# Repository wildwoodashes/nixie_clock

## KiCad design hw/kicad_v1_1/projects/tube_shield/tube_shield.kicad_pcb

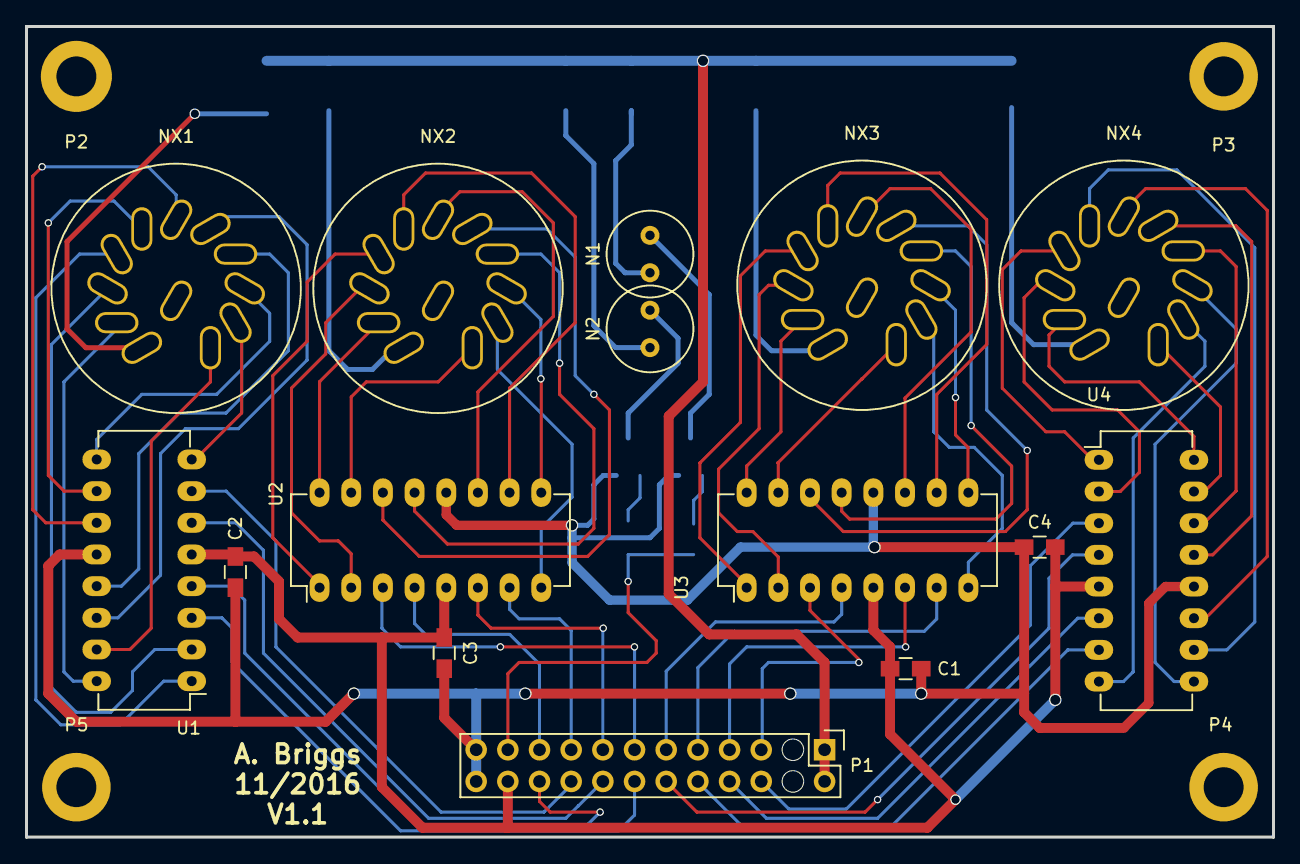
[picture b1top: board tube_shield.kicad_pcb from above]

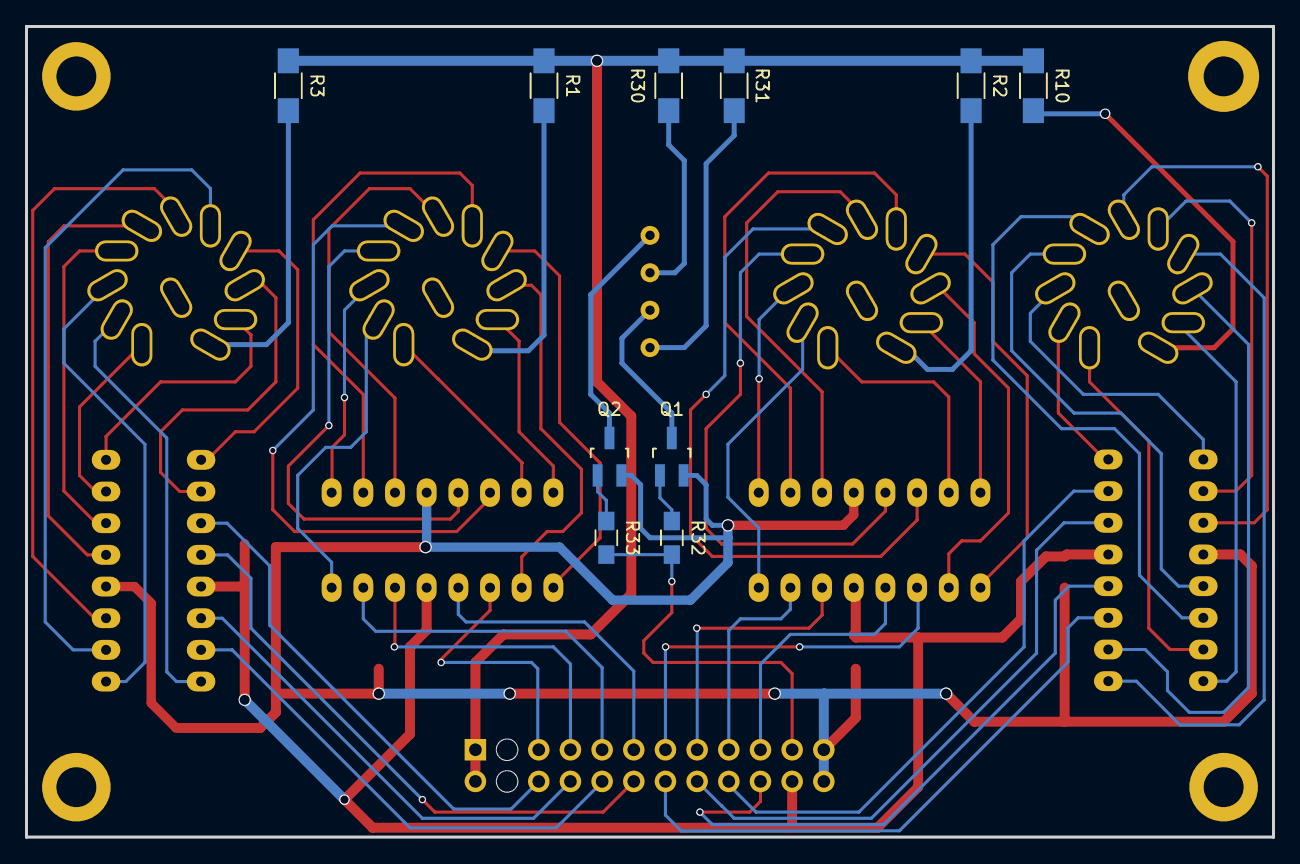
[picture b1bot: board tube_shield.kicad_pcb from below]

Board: 2 copper layers, 100.0 x 65.0 mm, 29 parts (10 on the bottom side), 70 nets.

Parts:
C1, C2, C3, C4: 0.1u; C_0805_HandSoldering
N1, N2: C2A; neon_ind
NX1, NX2, NX3, NX4: IN-8; pl27-1pd
P1: CONN_02X12_isolate_hv; Pin_Header_Straight_2x12_isolate_hv
P2: CONN_01X01; MountingHole_3.2mm_M3_ISO7380_Pad
P3, P4, P5: CONN_01X01; MountingHole_3.2mm_M3_ISO14580_Pad
Q1, Q2: MMBTA42; SOT-23_Handsoldering
R1, R2, R10: 15k; R_1206_HandSoldering
R3: 12k; R_1206_HandSoldering
R30, R31: 100k; R_1206_HandSoldering
R32, R33: 4.7k; R_0805_HandSoldering
U1, U2, U3, U4: K155ID1; DIP-16_W7.62mm_LongPads

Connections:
+5V: C1.1, C2.1, C3.1, C4.1, P1.22, U1.5, U2.5, U3.5, U4.5
+180V: P1.1, P1.2, R1.1, R2.1, R3.1, R10.1, R30.2, R31.2
/COL_SEL: P1.21, R32.2, R33.2
/N0_SEL_A: P1.14, U1.3
/N0_SEL_B: P1.16, U1.6
/N0_SEL_C: P1.18, U1.7
/N0_SEL_D: P1.20, U1.4
/N1_SEL_A: P1.13, U2.3
/N1_SEL_B: P1.15, U2.6
/N1_SEL_C: P1.17, U2.7
/N1_SEL_D: P1.19, U2.4
/N2_SEL_A: P1.5, U3.3
/N2_SEL_B: P1.7, U3.6
/N2_SEL_C: P1.9, U3.7
/N2_SEL_D: P1.11, U3.4
/N3_SEL_A: P1.6, U4.3
/N3_SEL_B: P1.8, U4.6
/N3_SEL_C: P1.10, U4.7
/N3_SEL_D: P1.12, U4.4
/Nixie Tubes/N0_A: NX1.11, R10.2
/Nixie Tubes/N0_CAT0: NX1.10, U1.16
/Nixie Tubes/N0_CAT1: NX1.1, U1.15
/Nixie Tubes/N0_CAT2: NX1.2, U1.8
/Nixie Tubes/N0_CAT3: NX1.3, U1.9
/Nixie Tubes/N0_CAT4: NX1.4, U1.13
/Nixie Tubes/N0_CAT5: NX1.5, U1.14
/Nixie Tubes/N0_CAT6: NX1.6, U1.11
/Nixie Tubes/N0_CAT7: NX1.7, U1.10
/Nixie Tubes/N0_CAT8: NX1.8, U1.1
/Nixie Tubes/N0_CAT9: NX1.9, U1.2
/Nixie Tubes/N1_A: NX2.11, R2.2
/Nixie Tubes/N1_CAT0: NX2.10, U2.16
/Nixie Tubes/N1_CAT1: NX2.1, U2.15
/Nixie Tubes/N1_CAT2: NX2.2, U2.8
/Nixie Tubes/N1_CAT3: NX2.3, U2.9
/Nixie Tubes/N1_CAT4: NX2.4, U2.13
/Nixie Tubes/N1_CAT5: NX2.5, U2.14
/Nixie Tubes/N1_CAT6: NX2.6, U2.11
/Nixie Tubes/N1_CAT7: NX2.7, U2.10
/Nixie Tubes/N1_CAT8: NX2.8, U2.1
/Nixie Tubes/N1_CAT9: NX2.9, U2.2
/Nixie Tubes/N2_A: NX3.11, R1.2
/Nixie Tubes/N2_CAT0: NX3.10, U3.16
/Nixie Tubes/N2_CAT1: NX3.1, U3.15
/Nixie Tubes/N2_CAT2: NX3.2, U3.8
/Nixie Tubes/N2_CAT3: NX3.3, U3.9
/Nixie Tubes/N2_CAT4: NX3.4, U3.13
/Nixie Tubes/N2_CAT5: NX3.5, U3.14
/Nixie Tubes/N2_CAT6: NX3.6, U3.11
/Nixie Tubes/N2_CAT7: NX3.7, U3.10
/Nixie Tubes/N2_CAT8: NX3.8, U3.1
/Nixie Tubes/N2_CAT9: NX3.9, U3.2
/Nixie Tubes/N3_A: NX4.11, R3.2
/Nixie Tubes/N3_CAT0: NX4.10, U4.16
/Nixie Tubes/N3_CAT1: NX4.1, U4.15
/Nixie Tubes/N3_CAT2: NX4.2, U4.8
/Nixie Tubes/N3_CAT3: NX4.3, U4.9
/Nixie Tubes/N3_CAT4: NX4.5, U4.13
/Nixie Tubes/N3_CAT5: NX4.4, U4.14
/Nixie Tubes/N3_CAT6: NX4.6, U4.11
/Nixie Tubes/N3_CAT7: NX4.7, U4.10
/Nixie Tubes/N3_CAT8: NX4.8, U4.1
/Nixie Tubes/N3_CAT9: NX4.9, U4.2
GND: C1.2, C2.2, C3.2, C4.2, P1.23, P1.24, Q1.2, Q2.2, U1.12, U2.12, U3.12, U4.12
unnamed: N1.1, R30.1
unnamed: N1.2, Q2.3
unnamed: N2.1, R31.1
unnamed: N2.2, Q1.3
unnamed: Q1.1, R32.1
unnamed: Q2.1, R33.1

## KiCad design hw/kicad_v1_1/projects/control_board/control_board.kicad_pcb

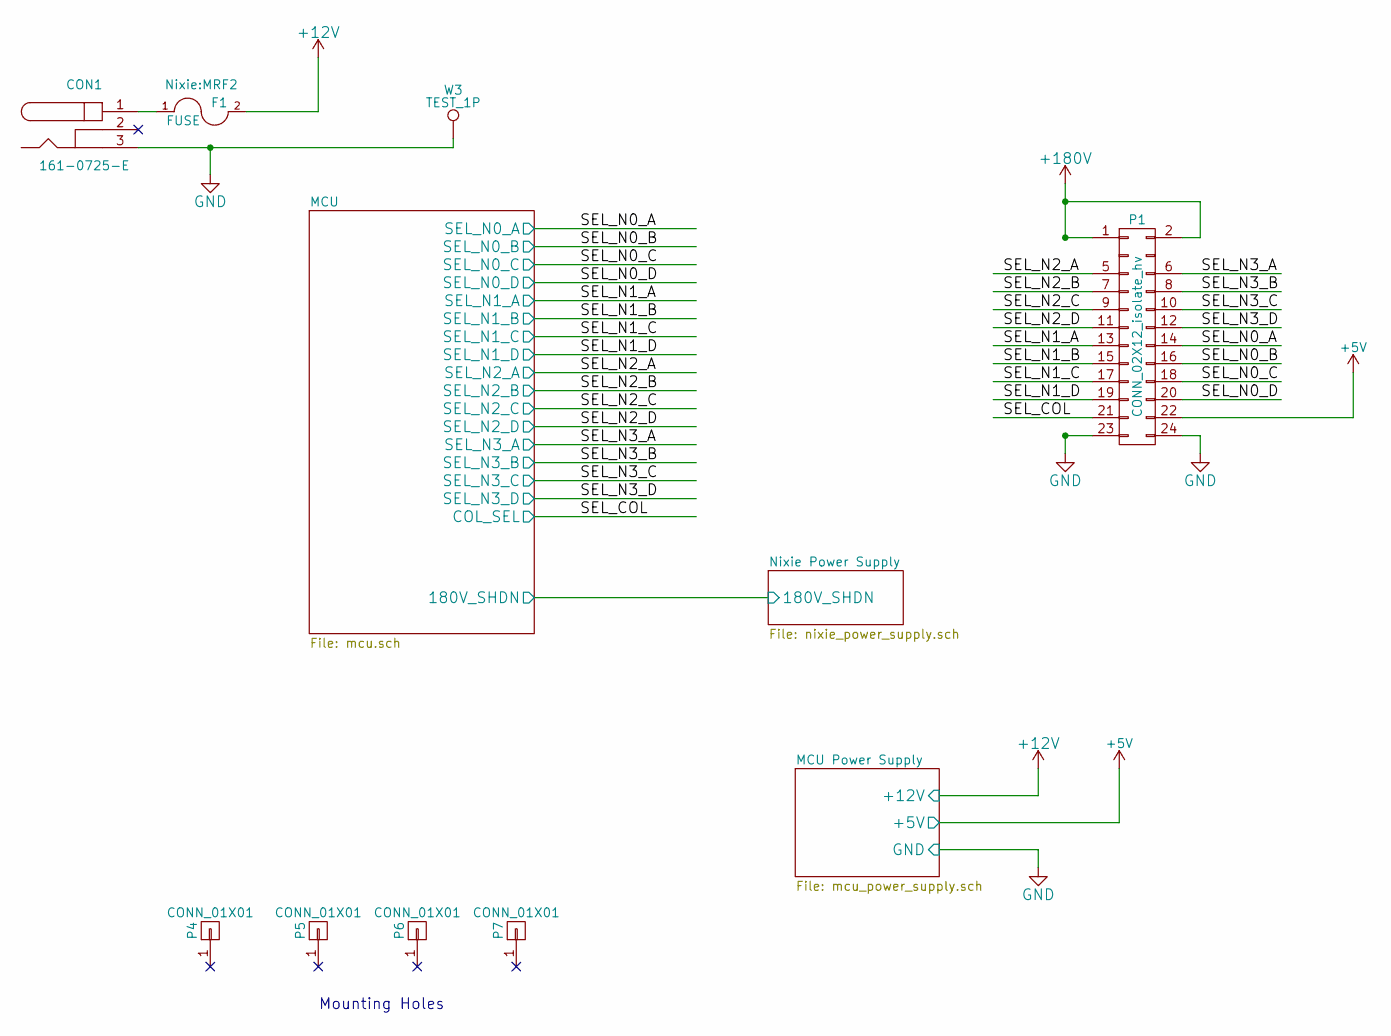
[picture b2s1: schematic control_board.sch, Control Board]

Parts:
CON1: 161-0725-E
F1: FUSE; MRF2
P1: CONN_02X12_isolate_hv
P4, P5, P6, P7: CONN_01X01; MountingHole_3.2mm_M3_ISO7380_Pad
W3: TEST_1P; Test_Point_Keystone_5019_Minature

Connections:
+5V: P1.22; also elsewhere on the board
+12V: F1.2; also elsewhere on the board
+180V: P1.1, P1.2; also elsewhere on the board
/SEL_COL: P1.21; also elsewhere on the board
/SEL_N0_A: P1.14; also elsewhere on the board
/SEL_N0_B: P1.16; also elsewhere on the board
/SEL_N0_C: P1.18; also elsewhere on the board
/SEL_N0_D: P1.20; also elsewhere on the board
/SEL_N1_A: P1.13; also elsewhere on the board
/SEL_N1_B: P1.15; also elsewhere on the board
/SEL_N1_C: P1.17; also elsewhere on the board
/SEL_N1_D: P1.19; also elsewhere on the board
/SEL_N2_A: P1.5; also elsewhere on the board
/SEL_N2_B: P1.7; also elsewhere on the board
/SEL_N2_C: P1.9; also elsewhere on the board
/SEL_N2_D: P1.11; also elsewhere on the board
/SEL_N3_A: P1.6; also elsewhere on the board
/SEL_N3_B: P1.8; also elsewhere on the board
/SEL_N3_C: P1.10; also elsewhere on the board
/SEL_N3_D: P1.12; also elsewhere on the board
GND: CON1.3, P1.23, P1.24, W3.1; also elsewhere on the board
unnamed: CON1.1, F1.1

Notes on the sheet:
Mounting Holes

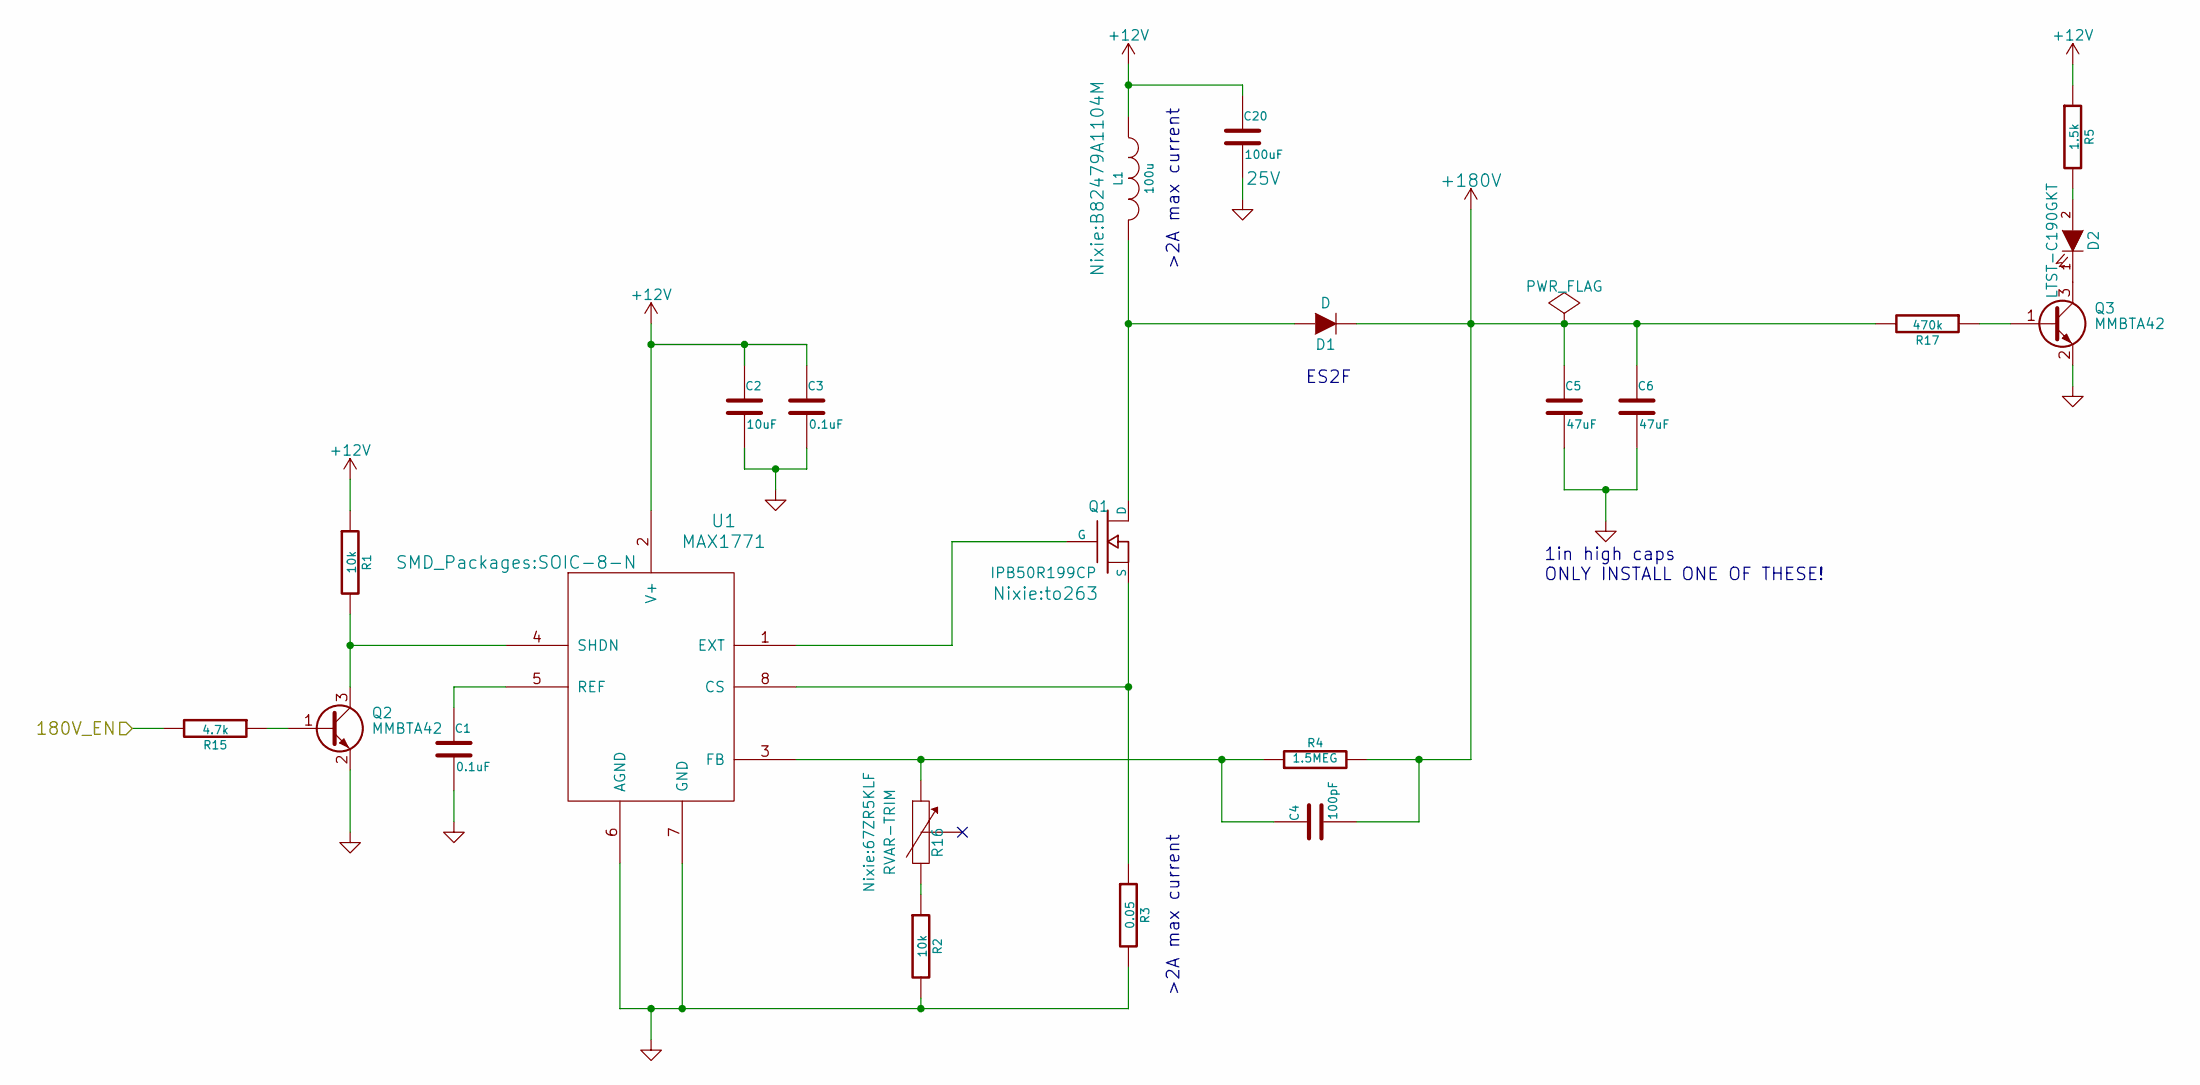
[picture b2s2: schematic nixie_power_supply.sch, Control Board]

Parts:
C1, C3: 0.1uF; C_0805_HandSoldering
C2: 10uF; C_1210_HandSoldering
C4: 100pF; C_0805_HandSoldering
C5, C6: 47uF; C_Radial_D12.5_L25_P5
C20: 100uF; c_elec_6.3x7.7; Voltage 25V
D1: D; DO-214AA-2
D2: LTST-C190GKT; LED_0603
L1: 100u; B82479A1104M
Q1: IPB50R199CP; to263
Q2, Q3: MMBTA42; SOT-23_Handsoldering
R1, R2: 10k; R_0805_HandSoldering
R3: 0.05; R_0805_HandSoldering
R4: 1.5MEG; R_1206_HandSoldering
R5: 1.5k; R_0805_HandSoldering
R15: 4.7k; R_0805_HandSoldering
R16: RVAR-TRIM; 67ZR5KLF
R17: 470k; R_0805_HandSoldering
U1: MAX1771; SOIC-8-N

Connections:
+12V: C2.1, C3.1, C20.1, L1.1, R1.1, R5.1, U1.2 (V+); also elsewhere on the board
+180V: C4.2, C5.1, C6.1, D1.1 (K), R4.2, R17.2; also elsewhere on the board
GND: C1.2, C2.2, C3.2, C5.2, C6.2, C20.2, Q2.2 (E), Q3.2 (E), R2.2, R3.2, U1.6 (AGND), U1.7 (GND); also elsewhere on the board
unnamed: C1.1, U1.5 (REF)
unnamed: C4.1, R4.1, R16.1, U1.3 (FB)
unnamed: D1.2 (A), L1.2, Q1.2 (D)
unnamed: D2.1 (K), Q3.3 (C)
unnamed: D2.2 (A), R5.2
unnamed: Q1.1 (G), U1.1 (EXT)
unnamed: Q1.3 (S), R3.1, U1.8 (CS)
unnamed: Q2.1 (B), R15.1
unnamed: Q3.1 (B), R17.1
unnamed: R2.1, R16.2

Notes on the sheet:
1in high caps ONLY INSTALL ONE OF THESE!
ES2F
>2A max current

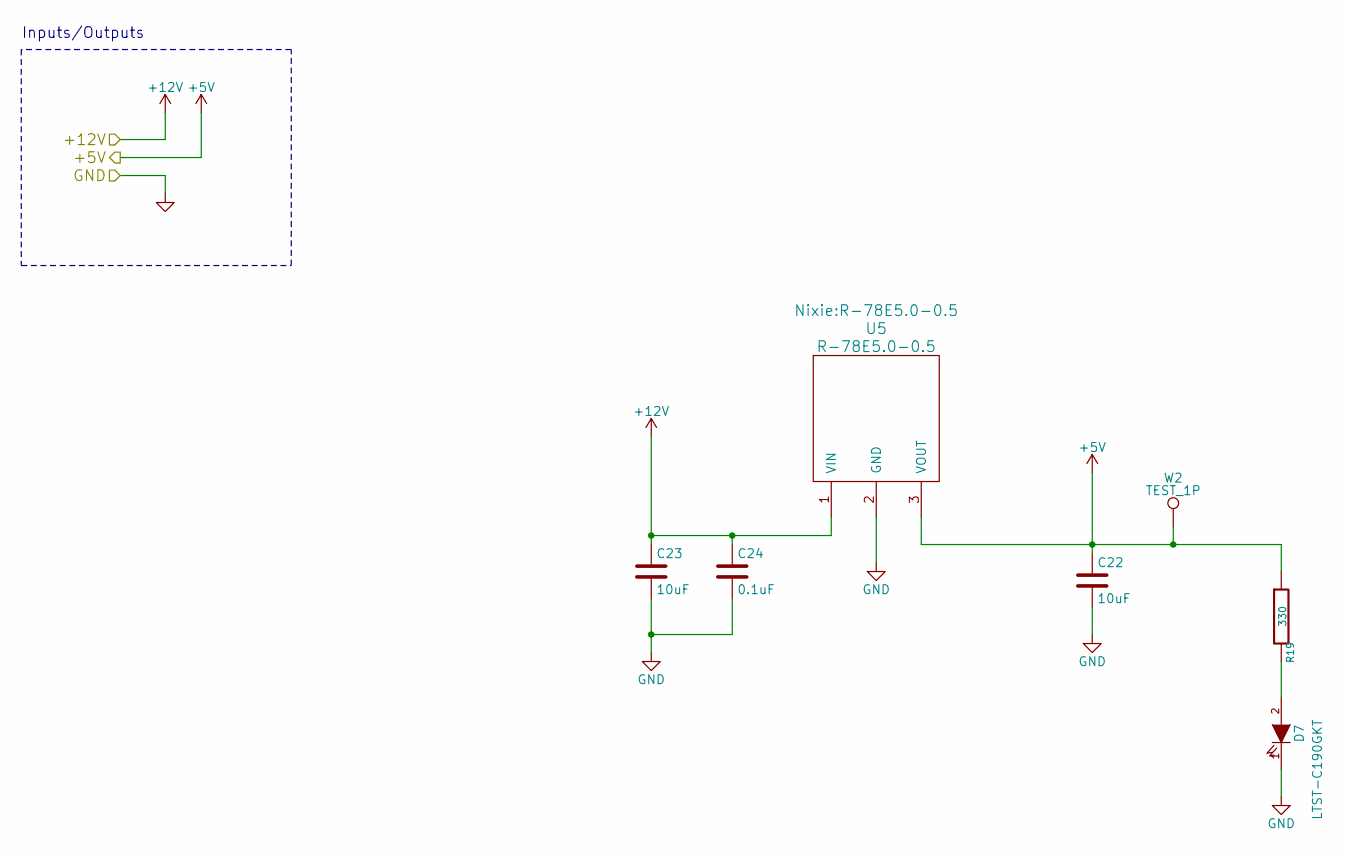
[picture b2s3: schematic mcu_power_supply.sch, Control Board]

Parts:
C22, C23: 10uF; C_0805_HandSoldering
C24: 0.1uF; C_0805_HandSoldering
D7: LTST-C190GKT; LED_0603
R19: 330; R_0805_HandSoldering
U5: R-78E5.0-0.5
W2: TEST_1P; Measurement_Point_Round-TH_Big

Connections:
+5V: C22.1, R19.1, U5.3 (VOUT), W2.1; also elsewhere on the board
+12V: C23.1, C24.1, U5.1 (VIN); also elsewhere on the board
GND: C22.2, C23.2, C24.2, D7.1 (K), U5.2 (GND); also elsewhere on the board
unnamed: D7.2 (A), R19.2

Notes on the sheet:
Inputs/Outputs

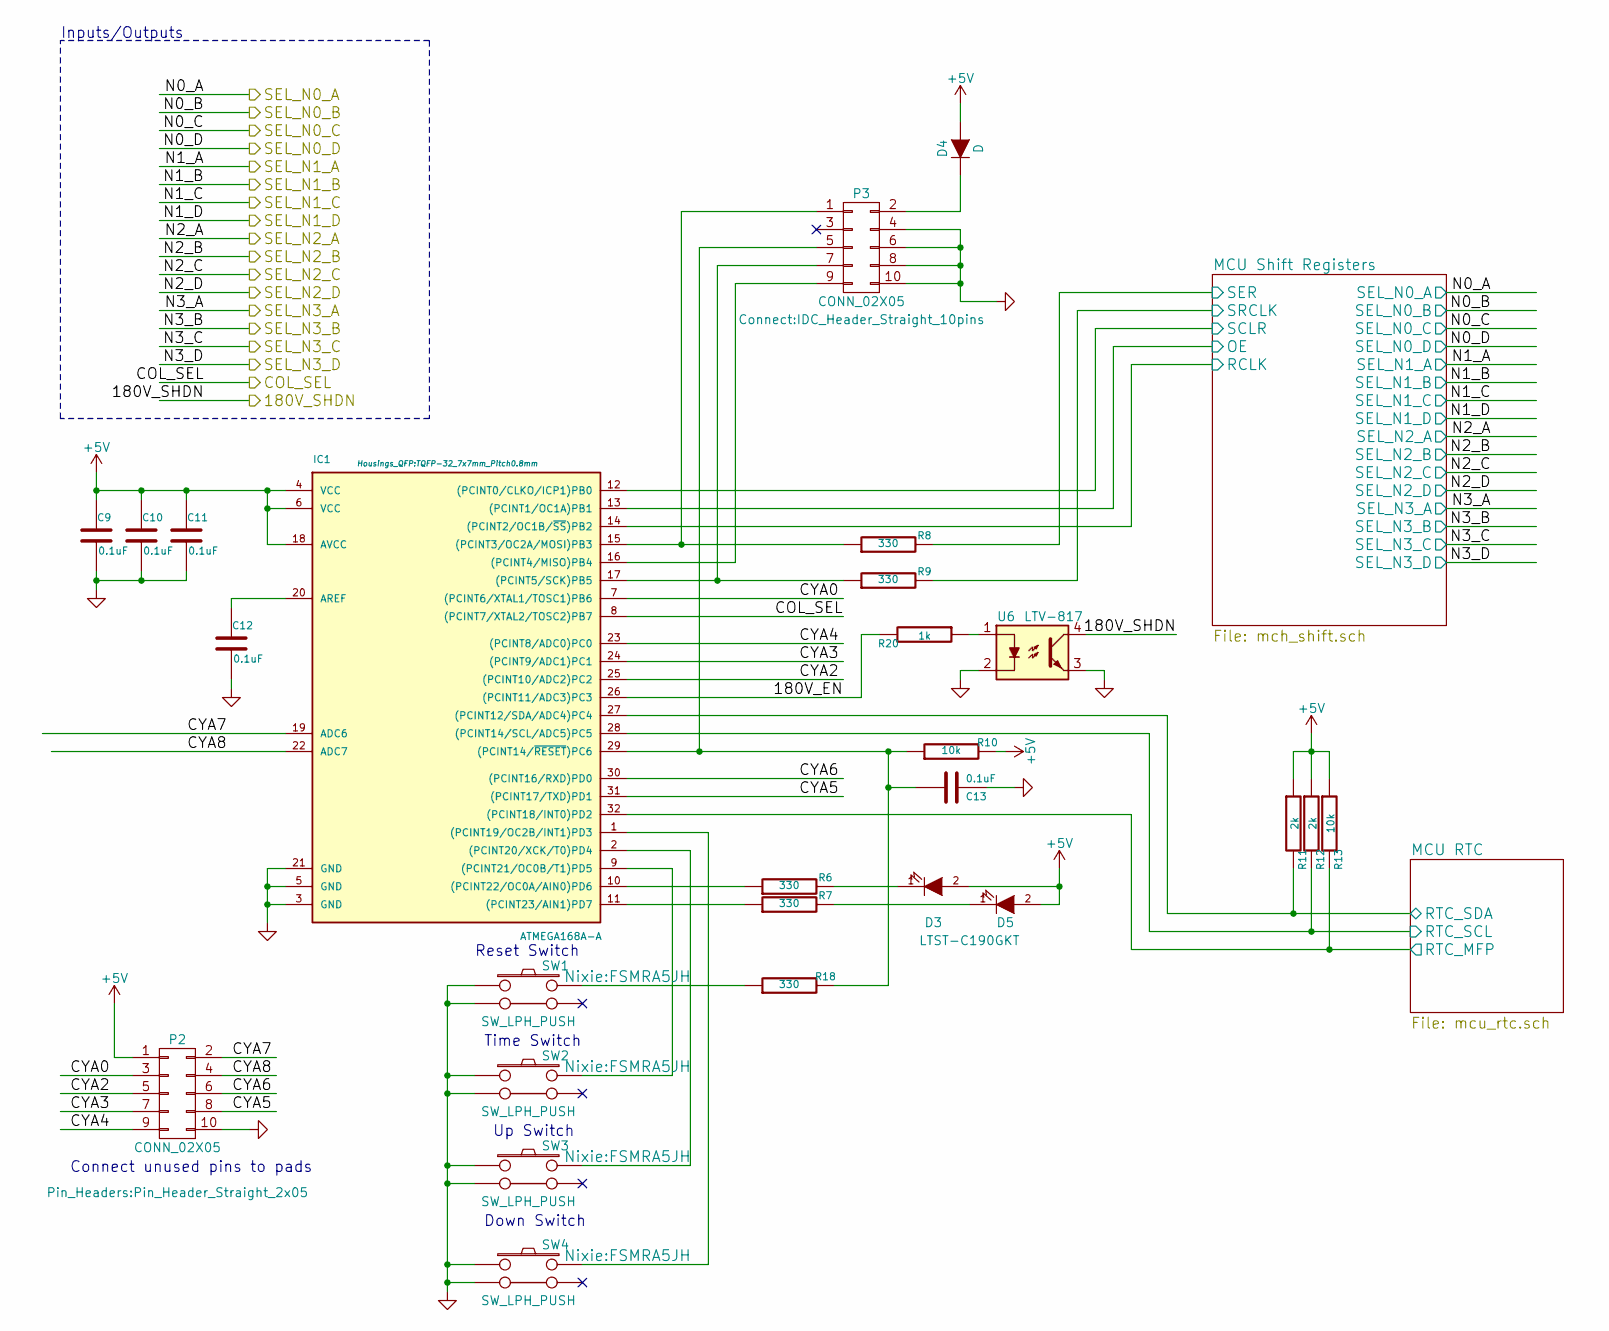
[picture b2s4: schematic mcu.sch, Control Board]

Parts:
C9, C10, C11, C12, C13: 0.1uF; C_0805_HandSoldering
D3, D5: LTST-C190GKT; LED_0603
D4: D; SOD-523-2
IC1: ATMEGA168A-A; TQFP-32_7x7mm_Pitch0.8mm
P2: CONN_02X05; Pin_Header_Straight_2x05
P3: CONN_02X05; IDC_Header_Straight_10pins
R6, R7, R8, R9, R18: 330; R_0805_HandSoldering
R10, R13: 10k; R_0805_HandSoldering
R11, R12: 2k; R_0805_HandSoldering
R20: 1k; R_0805_HandSoldering
SW1, SW2, SW3, SW4: SW_LPH_PUSH; FSMRA5JH
U6: LTV-817; Optocoupler_SMD_LTV-817S

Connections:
+5V: C9.1, C10.1, C11.1, D3.2 (A), D4.2 (A), D5.2 (A), IC1.4 (VCC), IC1.6 (VCC), IC1.18 (AVCC), P2.1, R10.2, R11.1, R12.1, R13.1; also elsewhere on the board
/MCU/180V_EN: IC1.26 ((PCINT11/ADC3)PC3), R20.2
/MCU/CYA0: IC1.7 ((PCINT6/XTAL1/TOSC1)PB6), P2.3
/MCU/CYA2: IC1.25 ((PCINT10/ADC2)PC2), P2.5
/MCU/CYA3: IC1.24 ((PCINT9/ADC1)PC1), P2.7
/MCU/CYA4: IC1.23 ((PCINT8/ADC0)PC0), P2.9
/MCU/CYA5: IC1.31 ((PCINT17/TXD)PD1), P2.8
/MCU/CYA6: IC1.30 ((PCINT16/RXD)PD0), P2.6
/MCU/CYA7: IC1.19 (ADC6), P2.2
/MCU/CYA8: IC1.22 (ADC7), P2.4
/MCU/MCU RTC/RTC_MFP: IC1.32 ((PCINT18/INT0)PD2), R13.2; also elsewhere on the board
/MCU/MCU RTC/RTC_SCL: IC1.28 ((PCINT14/SCL/ADC5)PC5), R12.2; also elsewhere on the board
/MCU/MCU RTC/RTC_SDA: IC1.27 ((PCINT12/SDA/ADC4)PC4), R11.2; also elsewhere on the board
/MCU/MCU Shift Registers/OE: IC1.13 ((PCINT1/OC1A)PB1); also elsewhere on the board
/MCU/MCU Shift Registers/RCLK: IC1.14 ((PCINT2/OC1B/~SS~)PB2); also elsewhere on the board
/MCU/MCU Shift Registers/SCLR: IC1.12 ((PCINT0/CLKO/ICP1)PB0); also elsewhere on the board
/MCU/MCU Shift Registers/SER: R8.2; also elsewhere on the board
/MCU/MCU Shift Registers/SRCLK: R9.2; also elsewhere on the board
/SEL_COL: IC1.8 ((PCINT7/XTAL2/TOSC2)PB7); also elsewhere on the board
GND: C9.2, C10.2, C11.2, C12.2, C13.2, IC1.3 (GND), IC1.5 (GND), IC1.21 (GND), P2.10, P3.4, P3.6, P3.8, P3.10, SW1.1, SW1.4, SW2.1, SW2.4, SW3.1, SW3.4, SW4.1, SW4.4, U6.2, U6.3; also elsewhere on the board
unnamed: C12.1, IC1.20 (AREF)
unnamed: C13.1, IC1.29 ((PCINT14/~RESET~)PC6), P3.5, R10.1, R18.2
unnamed: D3.1 (K), R6.2
unnamed: D4.1 (K), P3.2
unnamed: D5.1 (K), R7.2
unnamed: IC1.1 ((PCINT19/OC2B/INT1)PD3), SW4.2
unnamed: IC1.2 ((PCINT20/XCK/T0)PD4), SW3.2
unnamed: IC1.9 ((PCINT21/OC0B/T1)PD5), SW2.2
unnamed: IC1.10 ((PCINT22/OC0A/AIN0)PD6), R6.1
unnamed: IC1.11 ((PCINT23/AIN1)PD7), R7.1
unnamed: IC1.15 ((PCINT3/OC2A/MOSI)PB3), P3.1, R8.1
unnamed: IC1.16 ((PCINT4/MISO)PB4), P3.9
unnamed: IC1.17 ((PCINT5/SCK)PB5), P3.7, R9.1
unnamed: R18.1, SW1.2
unnamed: R20.1, U6.1

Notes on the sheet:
Inputs/Outputs
Reset Switch
Time Switch
Up Switch
Down Switch
Connect unused pins to pads

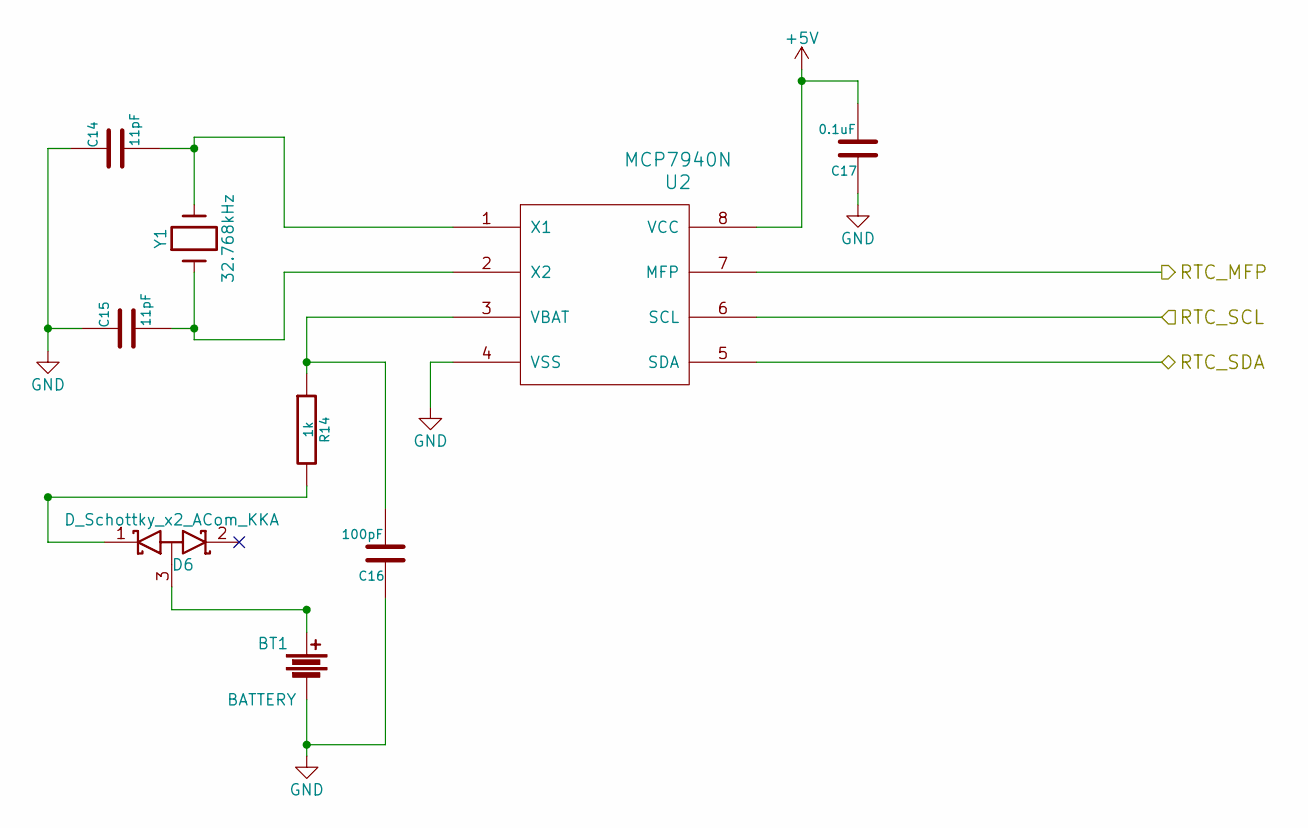
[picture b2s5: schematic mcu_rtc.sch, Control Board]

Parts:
BT1: BATTERY; smtu2032-c
C14, C15: 11pF; C_0603_HandSoldering
C16: 100pF; C_0805_HandSoldering
C17: 0.1uF; C_0805_HandSoldering
D6: D_Schottky_x2_ACom_KKA; SOT-323
R14: 1k; R_0805_HandSoldering
U2: MCP7940N; SOIC-8_3.9x4.9mm_Pitch1.27mm
Y1: 32.768kHz; ABS25

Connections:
+5V: C17.2, U2.8 (VCC); also elsewhere on the board
/MCU/MCU RTC/RTC_MFP: U2.7 (MFP); also elsewhere on the board
/MCU/MCU RTC/RTC_SCL: U2.6 (SCL); also elsewhere on the board
/MCU/MCU RTC/RTC_SDA: U2.5 (SDA); also elsewhere on the board
GND: BT1.2, C14.1, C15.1, C16.1, C17.1, U2.4 (VSS); also elsewhere on the board
unnamed: BT1.1, D6.3 (A)
unnamed: C14.2, U2.1 (X1), Y1.2
unnamed: C15.2, U2.2 (X2), Y1.1
unnamed: C16.2, R14.1, U2.3 (VBAT)
unnamed: D6.1 (K), R14.2

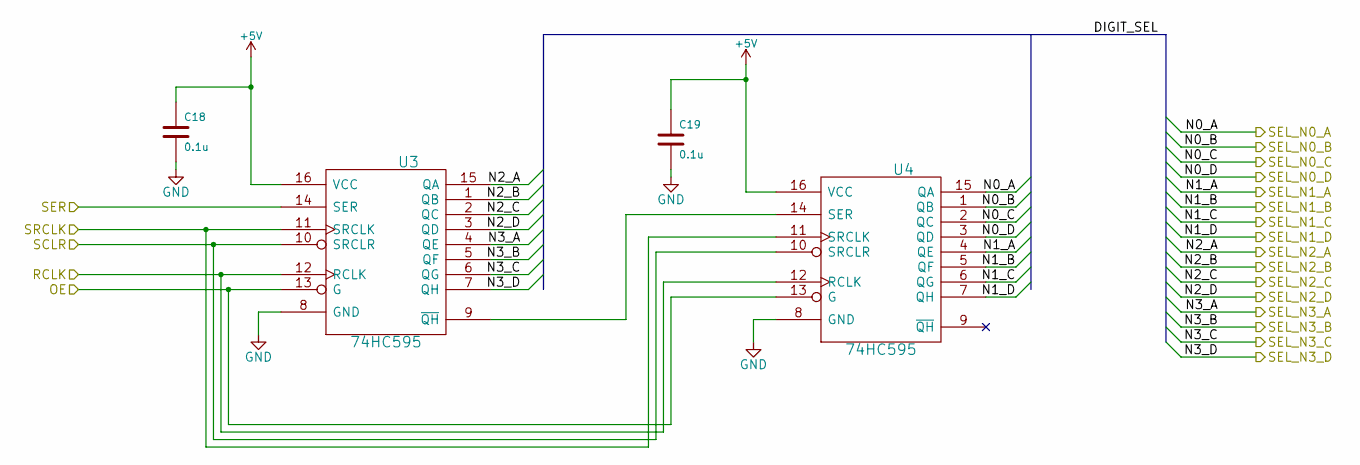
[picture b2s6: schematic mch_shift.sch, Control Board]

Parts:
C18, C19: 0.1u; C_0805_HandSoldering
U3, U4: 74HC595; SOIC-16_3.9x9.9mm_Pitch1.27mm

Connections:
+5V: C18.1, C19.1, U3.16 (VCC), U4.16 (VCC); also elsewhere on the board
/MCU/MCU Shift Registers/OE: U3.13 (G), U4.13 (G); also elsewhere on the board
/MCU/MCU Shift Registers/RCLK: U3.12 (RCLK), U4.12 (RCLK); also elsewhere on the board
/MCU/MCU Shift Registers/SCLR: U3.10 (SRCLR), U4.10 (SRCLR); also elsewhere on the board
/MCU/MCU Shift Registers/SER: U3.14 (SER); also elsewhere on the board
/MCU/MCU Shift Registers/SRCLK: U3.11 (SRCLK), U4.11 (SRCLK); also elsewhere on the board
/SEL_N0_A: U4.15 (QA); also elsewhere on the board
/SEL_N0_B: U4.1 (QB); also elsewhere on the board
/SEL_N0_C: U4.2 (QC); also elsewhere on the board
/SEL_N0_D: U4.3 (QD); also elsewhere on the board
/SEL_N1_A: U4.4 (QE); also elsewhere on the board
/SEL_N1_B: U4.5 (QF); also elsewhere on the board
/SEL_N1_C: U4.6 (QG); also elsewhere on the board
/SEL_N1_D: U4.7 (QH); also elsewhere on the board
/SEL_N2_A: U3.15 (QA); also elsewhere on the board
/SEL_N2_B: U3.1 (QB); also elsewhere on the board
/SEL_N2_C: U3.2 (QC); also elsewhere on the board
/SEL_N2_D: U3.3 (QD); also elsewhere on the board
/SEL_N3_A: U3.4 (QE); also elsewhere on the board
/SEL_N3_B: U3.5 (QF); also elsewhere on the board
/SEL_N3_C: U3.6 (QG); also elsewhere on the board
/SEL_N3_D: U3.7 (QH); also elsewhere on the board
GND: C18.2, C19.2, U3.8 (GND), U4.8 (GND); also elsewhere on the board
unnamed: U3.9 (~QH), U4.14 (SER)

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
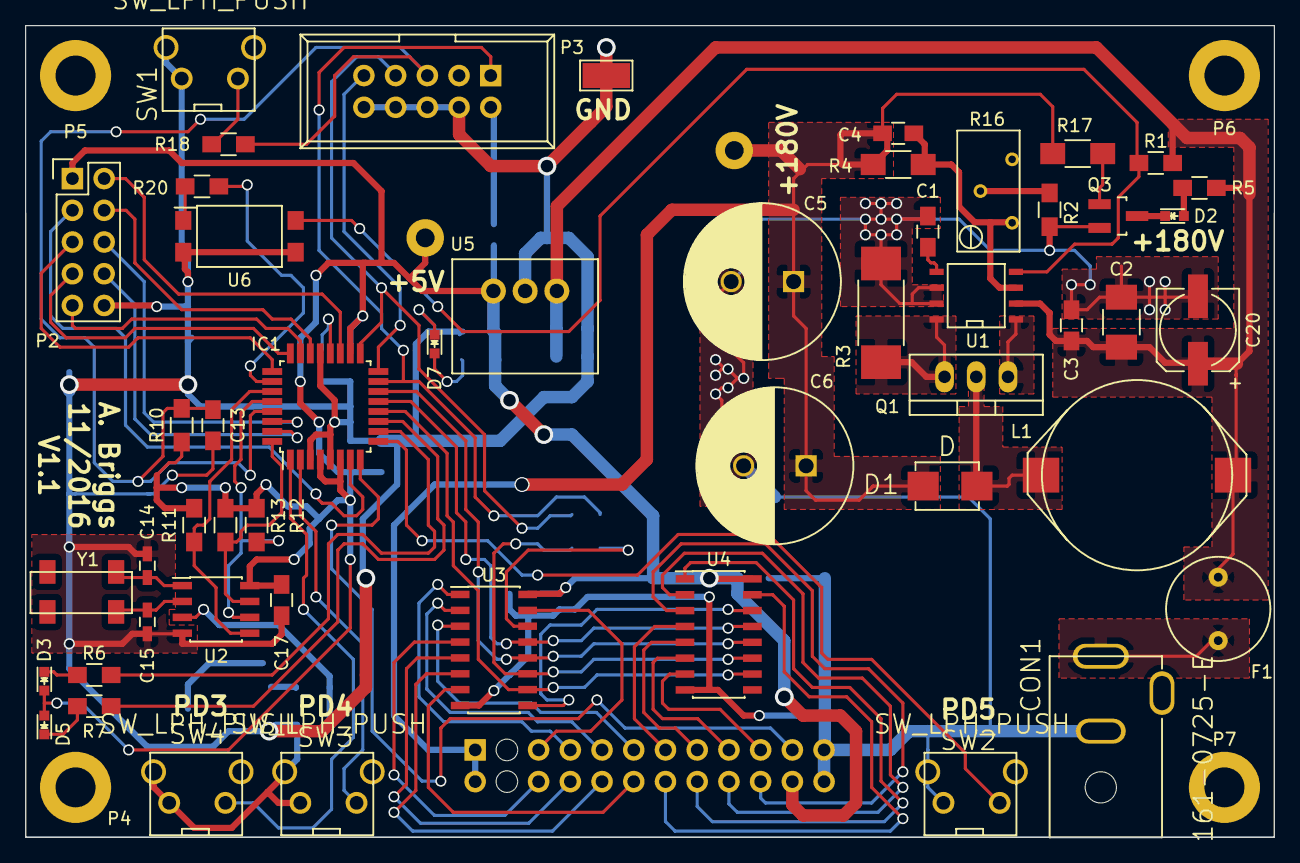
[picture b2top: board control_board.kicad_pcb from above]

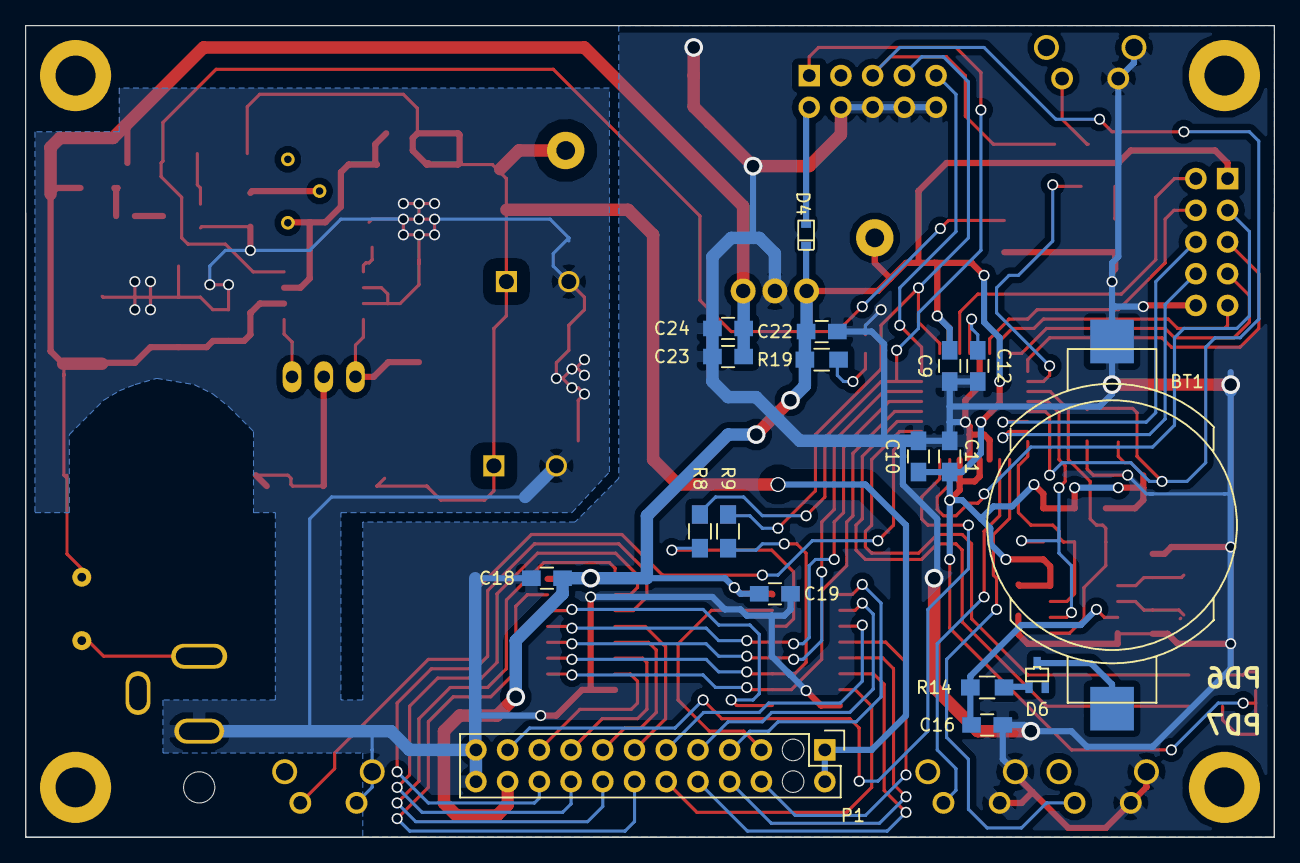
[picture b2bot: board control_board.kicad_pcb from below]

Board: 2 copper layers, 100.0 x 65.0 mm, 75 parts (19 on the bottom side), 71 nets.

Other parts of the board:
W1: TEST_1P; Measurement_Point_Round-TH_Big

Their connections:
+180V: W1.1; also elsewhere on the board
